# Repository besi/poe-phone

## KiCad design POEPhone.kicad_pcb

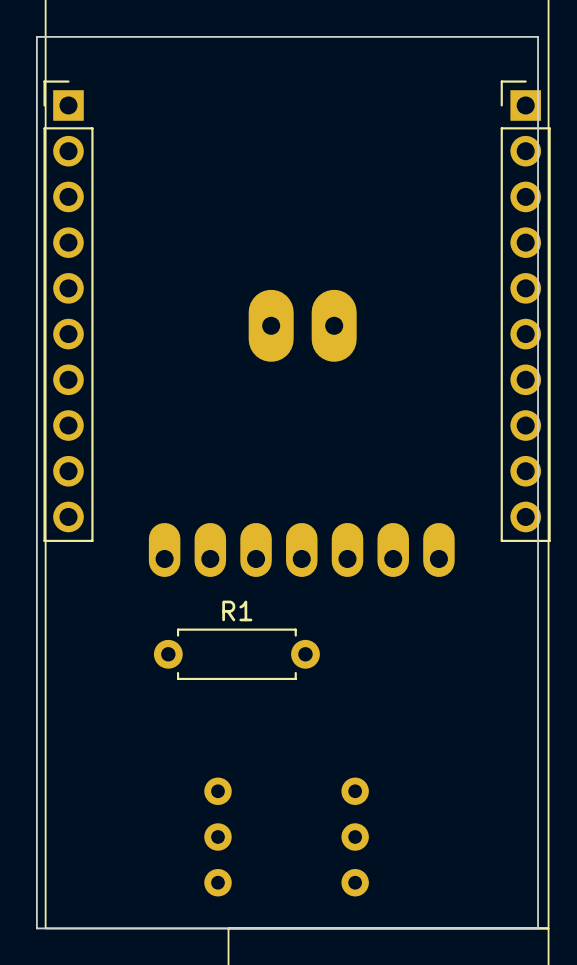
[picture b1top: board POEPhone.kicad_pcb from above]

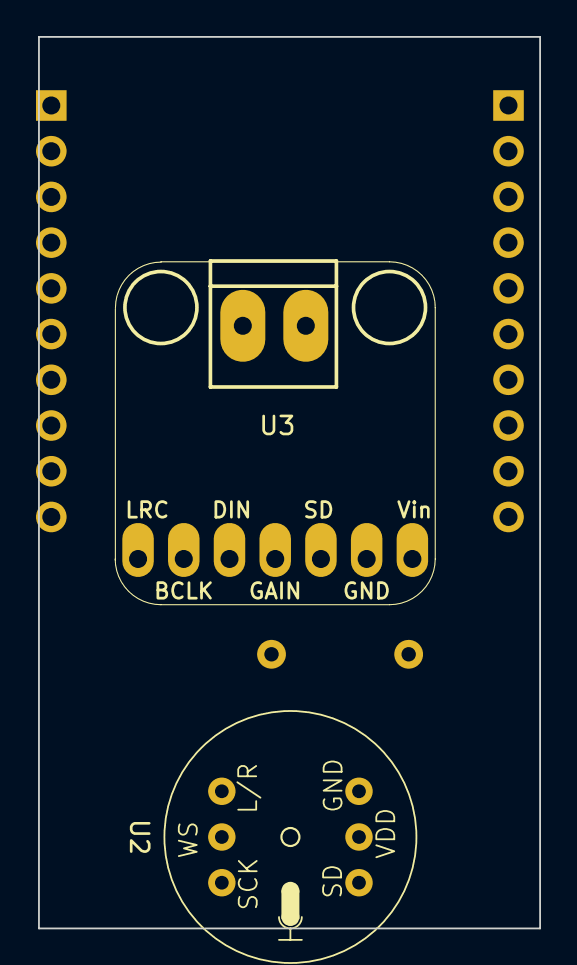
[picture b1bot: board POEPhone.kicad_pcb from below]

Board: 2 copper layers, 27.8 x 49.5 mm, 4 parts (2 on the bottom side), 6 nets, no tracks yet.

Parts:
R1: 100k; R_Axial_DIN0207_L6.3mm_D2.5mm_P7.62mm_Horizontal
U1: molex-poe
U2: mems-mic; mems-mic-round
U3: adafruit-MAX98357

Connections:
+3V3: U1.2 (3V3), U2.1 (3V), U3.1 (Vin)
GND: U1.3 (GND), U2.2 (GND), U2.6 (SEL), U3.2 (GND)
I2S_BCLK: U2.3 (BCLK), U3.6 (BCLK)
I2S_MIC_DATA: U1.12 (RX2/I36), U2.4 (DOUT)
I2S_RLCLK: U2.5 (LRCLK), U3.7 (LRC)
unnamed: R1.1, U3.4 (GAIN)

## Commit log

2024-03-14 Rough initial layout
